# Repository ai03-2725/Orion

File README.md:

# Orion
A prototype USB hub

### Warnings
* I am not an electrical engineer. This is all based on Google knowledge.
* The USB traces are only 6mil wide. Please verify that your PCB factory is capable of producing such thin traces.

### Features
* Just a USB Hub
* 4x downstream facing USB-A ports
* Upstream facing USB-C port
* ESD protection IC on every port
* Fuse on all downstream facing ports
* M2 mounting holes

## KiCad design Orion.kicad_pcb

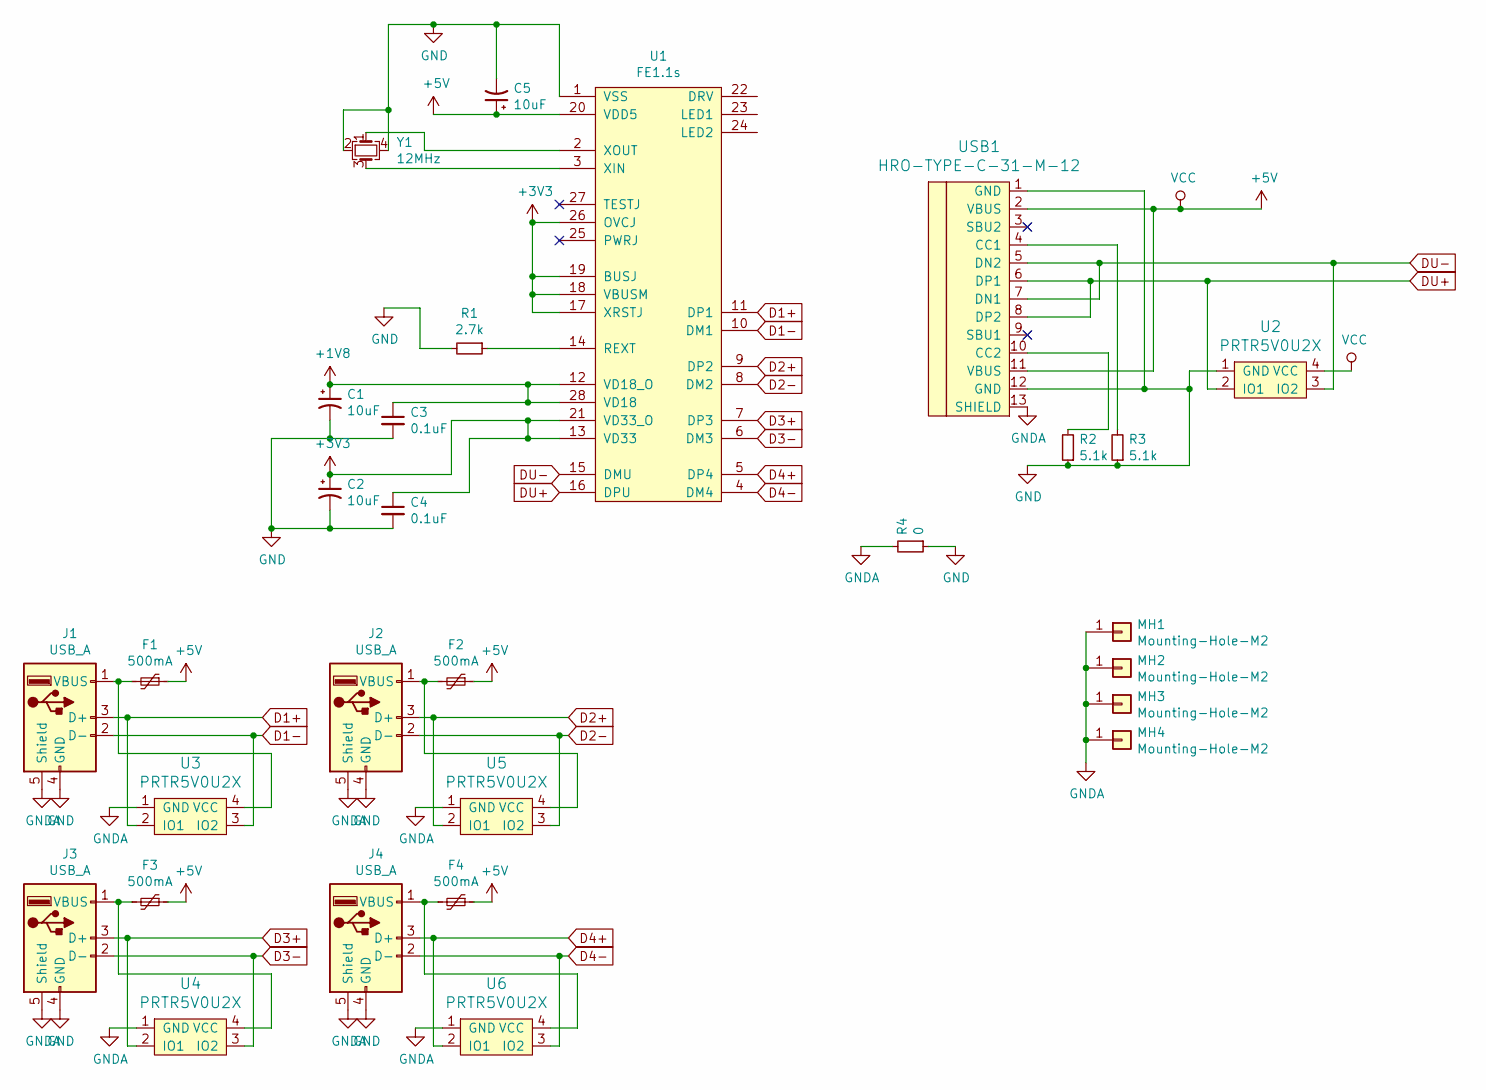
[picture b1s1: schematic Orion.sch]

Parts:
C1, C2, C5: 10uF; CP_Tantalum_Case-B_EIA-3528-21_Reflow
C3, C4: 0.1uF; C_0805
F1, F2, F3, F4: 500mA; Fuse_SMD1206_Reflow
J1, J2, J3, J4: USB_A; USB-A-Generic
MH1, MH2, MH3, MH4: Mounting-Hole-M2; MountingHole_2.2mm_M2_Pad_Via
R1: 2.7k; R_0805
R2, R3: 5.1k; R_0805
R4: 0; R_0805
U1: FE1.1s; SSOP-28_3.9x9.9mm_Pitch0.635mm
U2, U3, U4, U5, U6: PRTR5V0U2X; SOT143B
USB1: HRO-TYPE-C-31-M-12; HRO-TYPE-C-31-M-12-Assembly
Y1: 12MHz; Crystal_SMD_3225-4pin_3.2x2.5mm

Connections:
+1V8: C1.1, C3.1, U1.12 (VD18_O), U1.28 (VD18)
+3V3: C2.1, C4.1, U1.13 (VD33), U1.17 (XRSTJ), U1.18 (VBUSM), U1.19 (BUSJ), U1.21 (VD33_O), U1.26 (OVCJ)
+5V: C5.1, F1.1, F2.1, F3.1, F4.1, U1.20 (VDD5), U2.4 (VCC), USB1.2 (VBUS), USB1.11 (VBUS)
D1+: J1.3 (D+), U1.11 (DP1), U3.2 (IO1)
D1-: J1.2 (D-), U1.10 (DM1), U3.3 (IO2)
D2+: J2.3 (D+), U1.9 (DP2), U5.2 (IO1)
D2-: J2.2 (D-), U1.8 (DM2), U5.3 (IO2)
D3+: J3.3 (D+), U1.7 (DP3), U4.2 (IO1)
D3-: J3.2 (D-), U1.6 (DM3), U4.3 (IO2)
D4+: J4.3 (D+), U1.5 (DP4), U6.2 (IO1)
D4-: J4.2 (D-), U1.4 (DM4), U6.3 (IO2)
DU+: U1.16 (DPU), U2.2 (IO1), USB1.6 (DP1), USB1.8 (DP2)
DU-: U1.15 (DMU), U2.3 (IO2), USB1.5 (DN2), USB1.7 (DN1)
GND: C1.2, C2.2, C3.2, C4.2, C5.2, J1.4 (GND), J2.4 (GND), J3.4 (GND), J4.4 (GND), R1.2, R2.1, R3.1, R4.1, U1.1 (VSS), U2.1 (GND), USB1.1 (GND), USB1.12 (GND), Y1.2, Y1.4
GNDA: J1.5 (Shield), J2.5 (Shield), J3.5 (Shield), J4.5 (Shield), MH1.1, MH2.1, MH3.1, MH4.1, R4.2, U3.1 (GND), U4.1 (GND), U5.1 (GND), U6.1 (GND), USB1.13 (SHIELD)
unnamed: F1.2, J1.1 (VBUS), U3.4 (VCC)
unnamed: F2.2, J2.1 (VBUS), U5.4 (VCC)
unnamed: F3.2, J3.1 (VBUS), U4.4 (VCC)
unnamed: F4.2, J4.1 (VBUS), U6.4 (VCC)
unnamed: R1.1, U1.14 (REXT)
unnamed: R2.2, USB1.10 (CC2)
unnamed: R3.2, USB1.4 (CC1)
unnamed: U1.2 (XOUT), Y1.1
unnamed: U1.3 (XIN), Y1.3

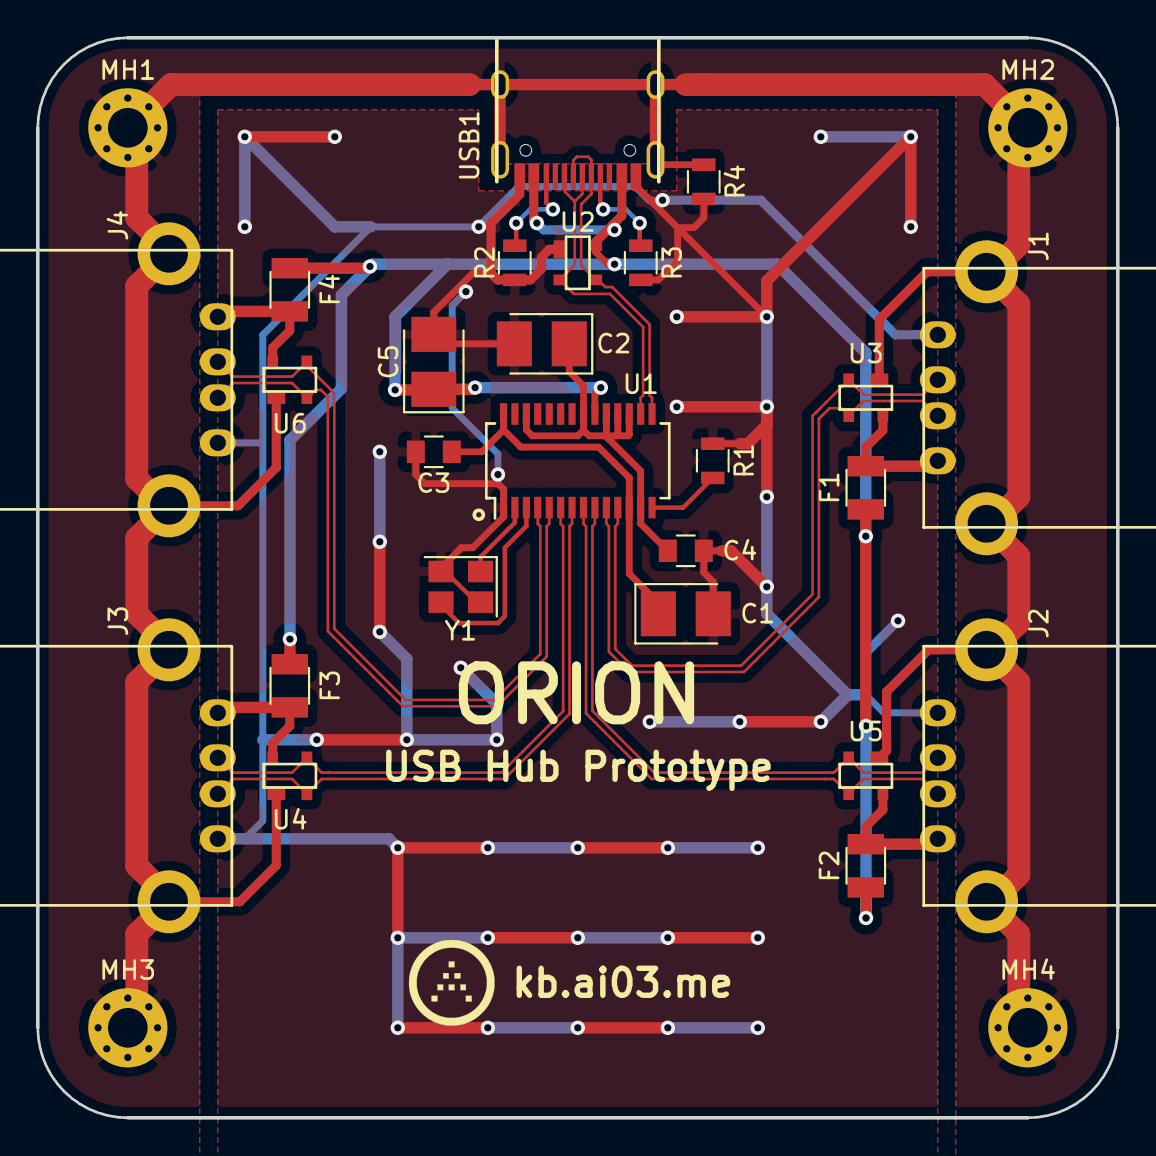
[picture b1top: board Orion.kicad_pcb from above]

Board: 2 copper layers, 60.0 x 60.0 mm, 29 parts (0 on the bottom side), 24 nets.

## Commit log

2019-03-25 Init Project
2019-03-25 Create generic USB hub
2019-03-25 Create production data
2019-03-25 Update submodules
2019-03-25 Add render
2019-03-25 New prod data
